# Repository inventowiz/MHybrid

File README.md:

MHybrid
=======

Repository for code/work done for the Michigan Hybrid Racing Team
=======

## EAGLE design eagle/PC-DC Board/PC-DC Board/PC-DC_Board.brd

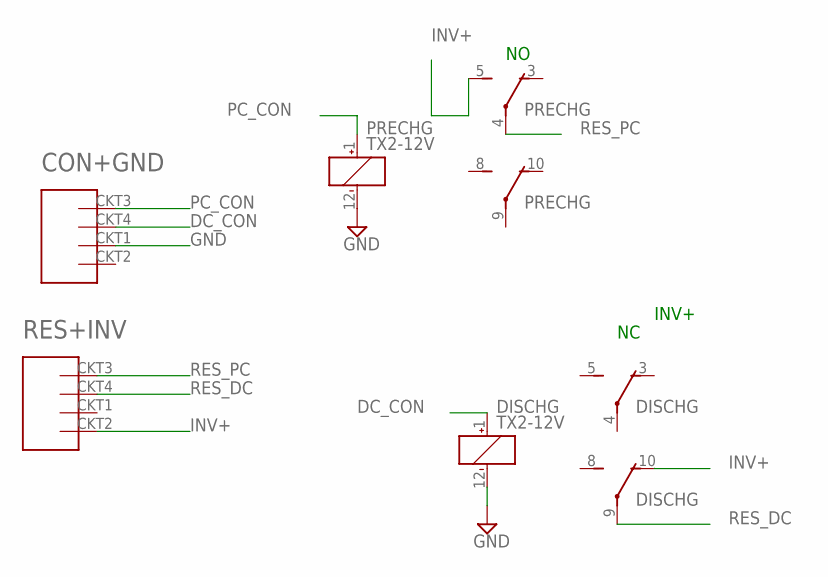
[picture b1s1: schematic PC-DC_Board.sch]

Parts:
CON+GND: MHYBRIDMOLEX; MOLEXMINIFIT6
DISCHG: TX2-12V; TX2
PRECHG: TX2-12V; TX2
RES+INV: MHYBRIDMOLEX; MOLEXMINIFIT6

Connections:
DC_CON: CON+GND.CKT4 (V_IN2(12)), DISCHG.1 (+)
GND: CON+GND.CKT1 (GND), DISCHG.12 (-), PRECHG.12 (-)
INV+: DISCHG.10 (O), PRECHG.5 (S), RES+INV.CKT2 (GND2)
PC_CON: CON+GND.CKT3 (V_IN(12)), PRECHG.1 (+)
RES_DC: DISCHG.9, RES+INV.CKT4 (V_IN2(12))
RES_PC: PRECHG.4, RES+INV.CKT3 (V_IN(12))

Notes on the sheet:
INV+

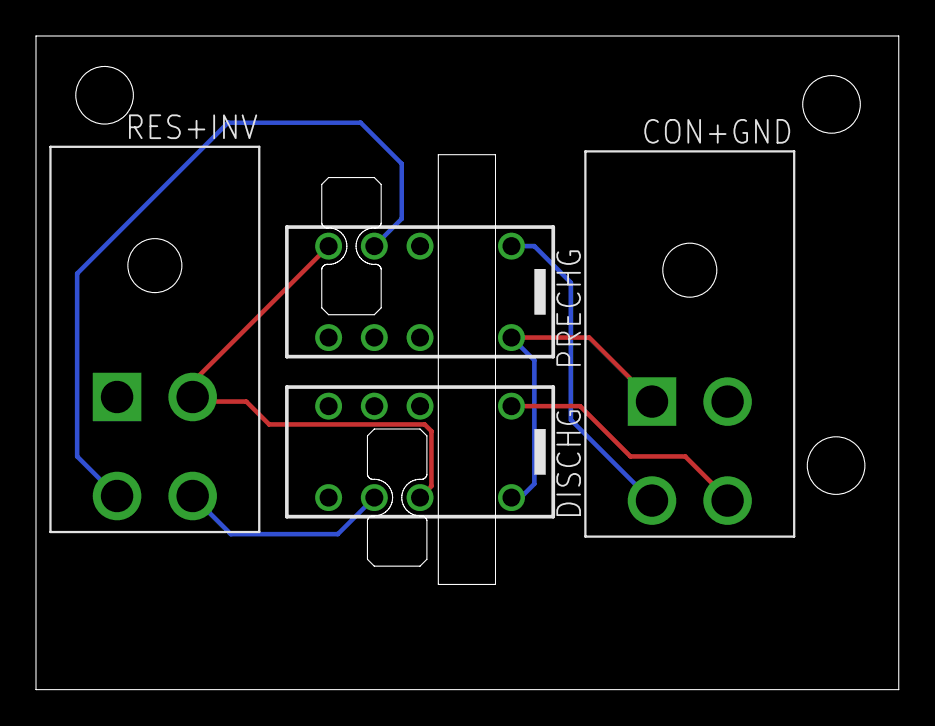
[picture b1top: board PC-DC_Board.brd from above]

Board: 2 copper layers, 47.9 x 36.3 mm, 4 parts (0 on the bottom side), 6 nets.

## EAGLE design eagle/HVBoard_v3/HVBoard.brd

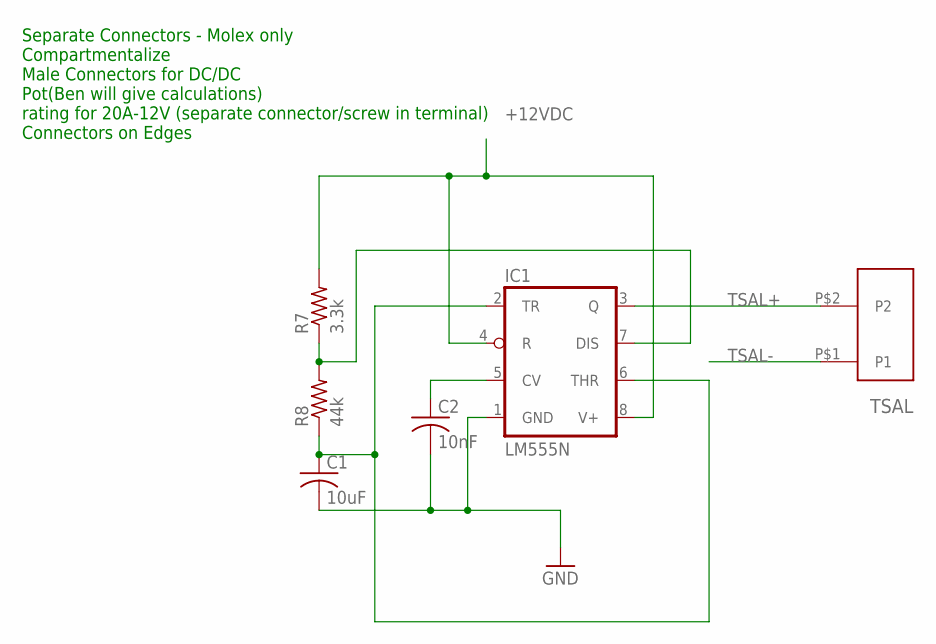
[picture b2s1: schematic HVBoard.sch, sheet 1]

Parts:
C1: 10uF; C025-025X050
C2: 10nF; C025-025X050
IC1: LM555N; DIL08
R7: 3.3k; 0207/7
R8: 44k; 0207/7
TSAL: MINIFIT_2PIN; 2PIN_MOLEXMINIFIT

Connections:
+12VDC: IC1.4 (R), IC1.8 (V+), R7.2; also elsewhere on the board
GND: C1.2, C2.2, IC1.1 (GND); also elsewhere on the board
unnamed: C1.1, IC1.2 (TR), IC1.6 (THR), R8.1
unnamed: IC1.7 (DIS), R7.1, R8.2
unnamed: C2.1, IC1.5 (CV)
TSAL+: IC1.3 (Q), TSAL.P$2 (P2)
TSAL-: TSAL.P$1 (P1); also elsewhere on the board

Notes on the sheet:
Separate Connectors - Molex only Compartmentalize Male Connectors for DC/DC Pot(Ben will give calculations) rating for 20A-12V (separate connector/screw in terminal) Connectors on Edges

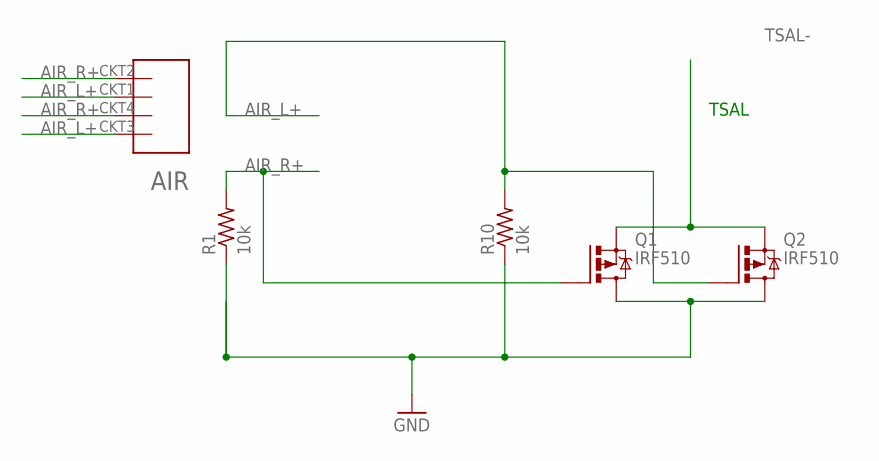
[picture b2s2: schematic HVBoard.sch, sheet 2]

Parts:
AIR: MHYBRIDMOLEX; MOLEXMINIFIT6
Q1, Q2: IRF510; TO220BV
R1, R10: 10k; 0207/7

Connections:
AIR_L+: AIR.CKT1 (GND), AIR.CKT3 (V_IN(12)), Q2.G, R10.2
AIR_R+: AIR.CKT2 (GND2), AIR.CKT4 (V_IN2(12)), Q1.G, R1.2
GND: Q1.D, Q2.D, R1.1, R10.1; also elsewhere on the board
TSAL-: Q1.S, Q2.S; also elsewhere on the board

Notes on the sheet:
TSAL

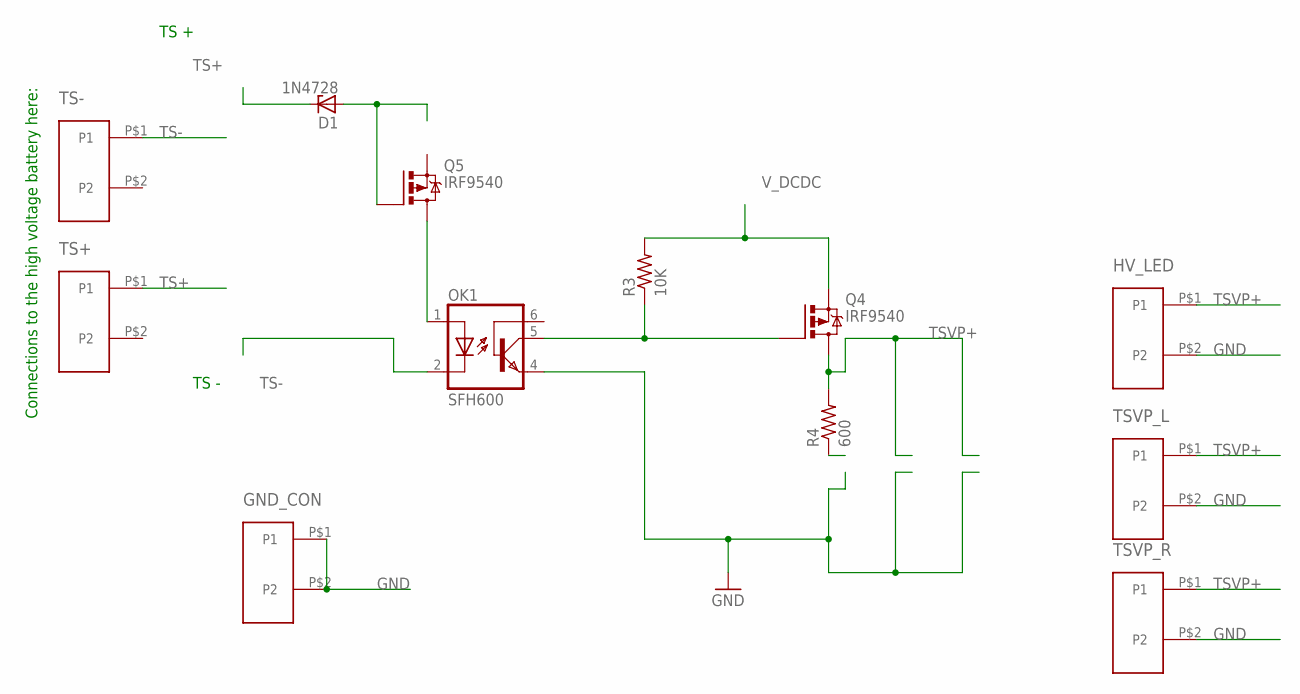
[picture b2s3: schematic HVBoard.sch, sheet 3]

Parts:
D1: 1N4728; DO41Z10
GND_CON: MINIFIT_2PIN; 2PIN_MOLEXMINIFIT
HV_LED: MINIFIT_2PIN; 2PIN_MOLEXMINIFIT
OK1: SFH600; DIL06
Q4, Q5: IRF9540; TO220BV
R3: 10K; R0603
R4: 600; R0603
TS+: MINIFIT_2PIN; 2PIN_MOLEXMINIFIT
TS-: MINIFIT_2PIN; 2PIN_MOLEXMINIFIT
TSVP_L: MINIFIT_2PIN; 2PIN_MOLEXMINIFIT
TSVP_R: MINIFIT_2PIN; 2PIN_MOLEXMINIFIT

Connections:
GND: GND_CON.P$1 (P1), GND_CON.P$2 (P2), HV_LED.P$2 (P2), OK1.4 (EMI), TSVP_L.P$2 (P2), TSVP_R.P$2 (P2); also elsewhere on the board
unnamed: OK1.5 (COL), Q4.G, R3.1
TS+: D1.C, TS+.P$1 (P1); also elsewhere on the board
TS+2: D1.A, Q5.G
TS+3: OK1.1 (A), Q5.D
TS-: OK1.2 (C), TS-.P$1 (P1); also elsewhere on the board
TSVP+: HV_LED.P$1 (P1), Q4.D, R4.2, TSVP_L.P$1 (P1), TSVP_R.P$1 (P1)
V_DCDC: Q4.S, R3.2; also elsewhere on the board

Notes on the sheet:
TS +
TS -
Connections to the high voltage battery here:

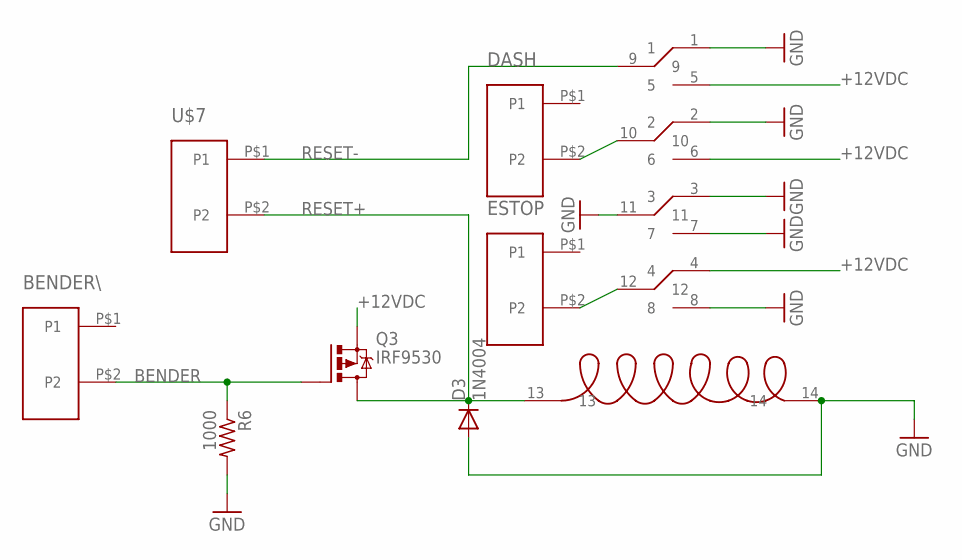
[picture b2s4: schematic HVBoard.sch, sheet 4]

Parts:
BENDER\: MINIFIT_2PIN; 2PIN_MOLEXMINIFIT
D3: 1N4004; DO41-10
DASH: MINIFIT_2PIN; 2PIN_MOLEXMINIFIT
ESTOP: MINIFIT_2PIN; 2PIN_MOLEXMINIFIT
NEW??1: HJ4-DC12VHJ4-DC12V; HJ4-DC12V
Q3: IRF9530; TO220BV
R6: 1000; M5923
U$7: MINIFIT_2PIN; 2PIN_MOLEXMINIFIT

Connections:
+12VDC: NEW??1.4, NEW??1.5, NEW??1.6, Q3.S; also elsewhere on the board
BENDER: BENDER\.P$2 (P2), Q3.G, R6.1
GND: D3.A, NEW??1.1, NEW??1.2, NEW??1.3, NEW??1.7, NEW??1.8, NEW??1.11, NEW??1.14, R6.2; also elsewhere on the board
unnamed: DASH.P$2 (P2), NEW??1.10
unnamed: ESTOP.P$2 (P2), NEW??1.12
RESET+: D3.C, NEW??1.13, Q3.D, U$7.P$2 (P2)
RESET-: NEW??1.9, U$7.P$1 (P1)

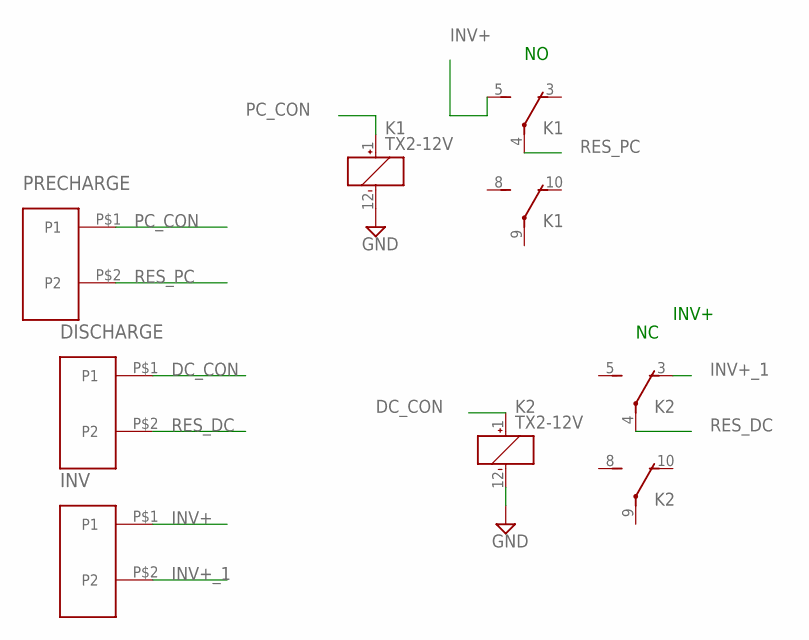
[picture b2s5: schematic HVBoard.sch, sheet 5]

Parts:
DISCHARGE: MINIFIT_2PIN; 2PIN_MOLEXMINIFIT
INV: MINIFIT_2PIN; 2PIN_MOLEXMINIFIT
K1, K2: TX2-12V; TX2
PRECHARGE: MINIFIT_2PIN; 2PIN_MOLEXMINIFIT

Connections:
DC_CON: DISCHARGE.P$1 (P1), K2.1 (+)
GND: K1.12 (-), K2.12 (-); also elsewhere on the board
INV+: INV.P$1 (P1), K1.5 (S)
INV+_1: INV.P$2 (P2), K2.3 (O)
PC_CON: K1.1 (+), PRECHARGE.P$1 (P1)
RES_DC: DISCHARGE.P$2 (P2), K2.4
RES_PC: K1.4, PRECHARGE.P$2 (P2)

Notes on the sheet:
INV+

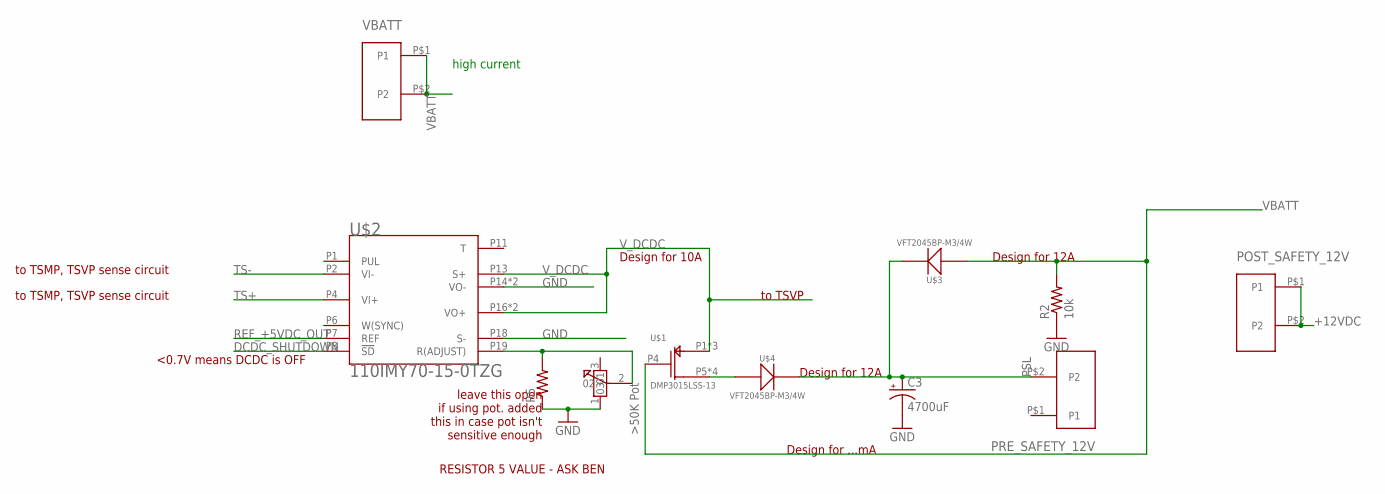
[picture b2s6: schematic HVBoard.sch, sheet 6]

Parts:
C3: 4700uF; CPOL-RADIAL-1000UF-63V
POST_SAFETY_12V: MINIFIT_2PIN; 2PIN_MOLEXMINIFIT
POT1: 3310P-001-503L-NP
PRE_SAFETY_12V: MINIFIT_2PIN; 2PIN_MOLEXMINIFIT
R2: 10k; R0603
R5: R-US_R0805; R0805
U$1: DMP3015LSS-13; 8-SOP
U$2: 110IMY70-15-0TZG
U$3, U$4: VFT2045BP-M3/4W
VBATT: MINIFIT_2PIN; 2PIN_MOLEXMINIFIT

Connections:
+12VDC: POST_SAFETY_12V.P$1 (P1), POST_SAFETY_12V.P$2 (P2); also elsewhere on the board
DCDC_SHUTDOWN: U$2.P8 (!SD)
GND: C3.2 (-), POT1.1, R2.1, R5.1, U$2.P14 (VO-), U$2.P15 (VO-), U$2.P18 (S-); also elsewhere on the board
unnamed: POT1.2, R5.2, U$2.P19 (R(ADJUST))
unnamed: U$1.P5 (D), U$1.P6 (D), U$1.P7 (D), U$1.P8 (D), U$4.P1
PSL: C3.1 (+), PRE_SAFETY_12V.P$2 (P2), U$3.P2, U$4.P2
REF_+5VDC_OUT: U$2.P7 (REF)
TS+: U$2.P4 (VI+); also elsewhere on the board
TS-: U$2.P2 (VI-); also elsewhere on the board
VBATT: R2.2, U$1.P4 (G), U$3.P1, VBATT.P$1 (P1), VBATT.P$2 (P2)
V_DCDC: U$1.P1 (S), U$1.P2 (S), U$1.P3 (S), U$2.P13 (S+), U$2.P16 (VO+), U$2.P17 (VO+); also elsewhere on the board

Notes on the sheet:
Design for 10A
Design for 12A
Design for ...mA
leave this open if using pot. added this in case pot isn't sensitive enough
<0.7V means DCDC is OFF
to TSVP
to TSMP, TSVP sense circuit
high current
RESISTOR 5 VALUE - ASK BEN

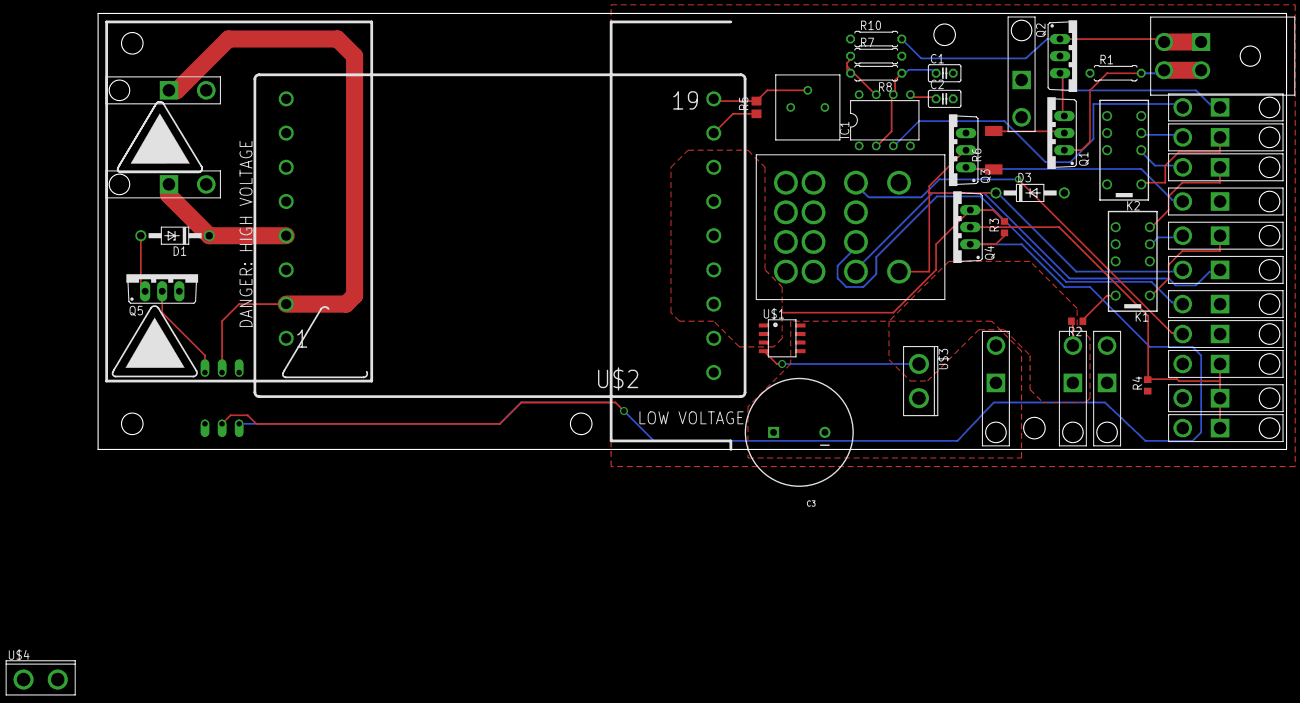
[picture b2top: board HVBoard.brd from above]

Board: 2 copper layers, 176.5 x 64.8 mm, 47 parts (1 on the bottom side), 31 nets.

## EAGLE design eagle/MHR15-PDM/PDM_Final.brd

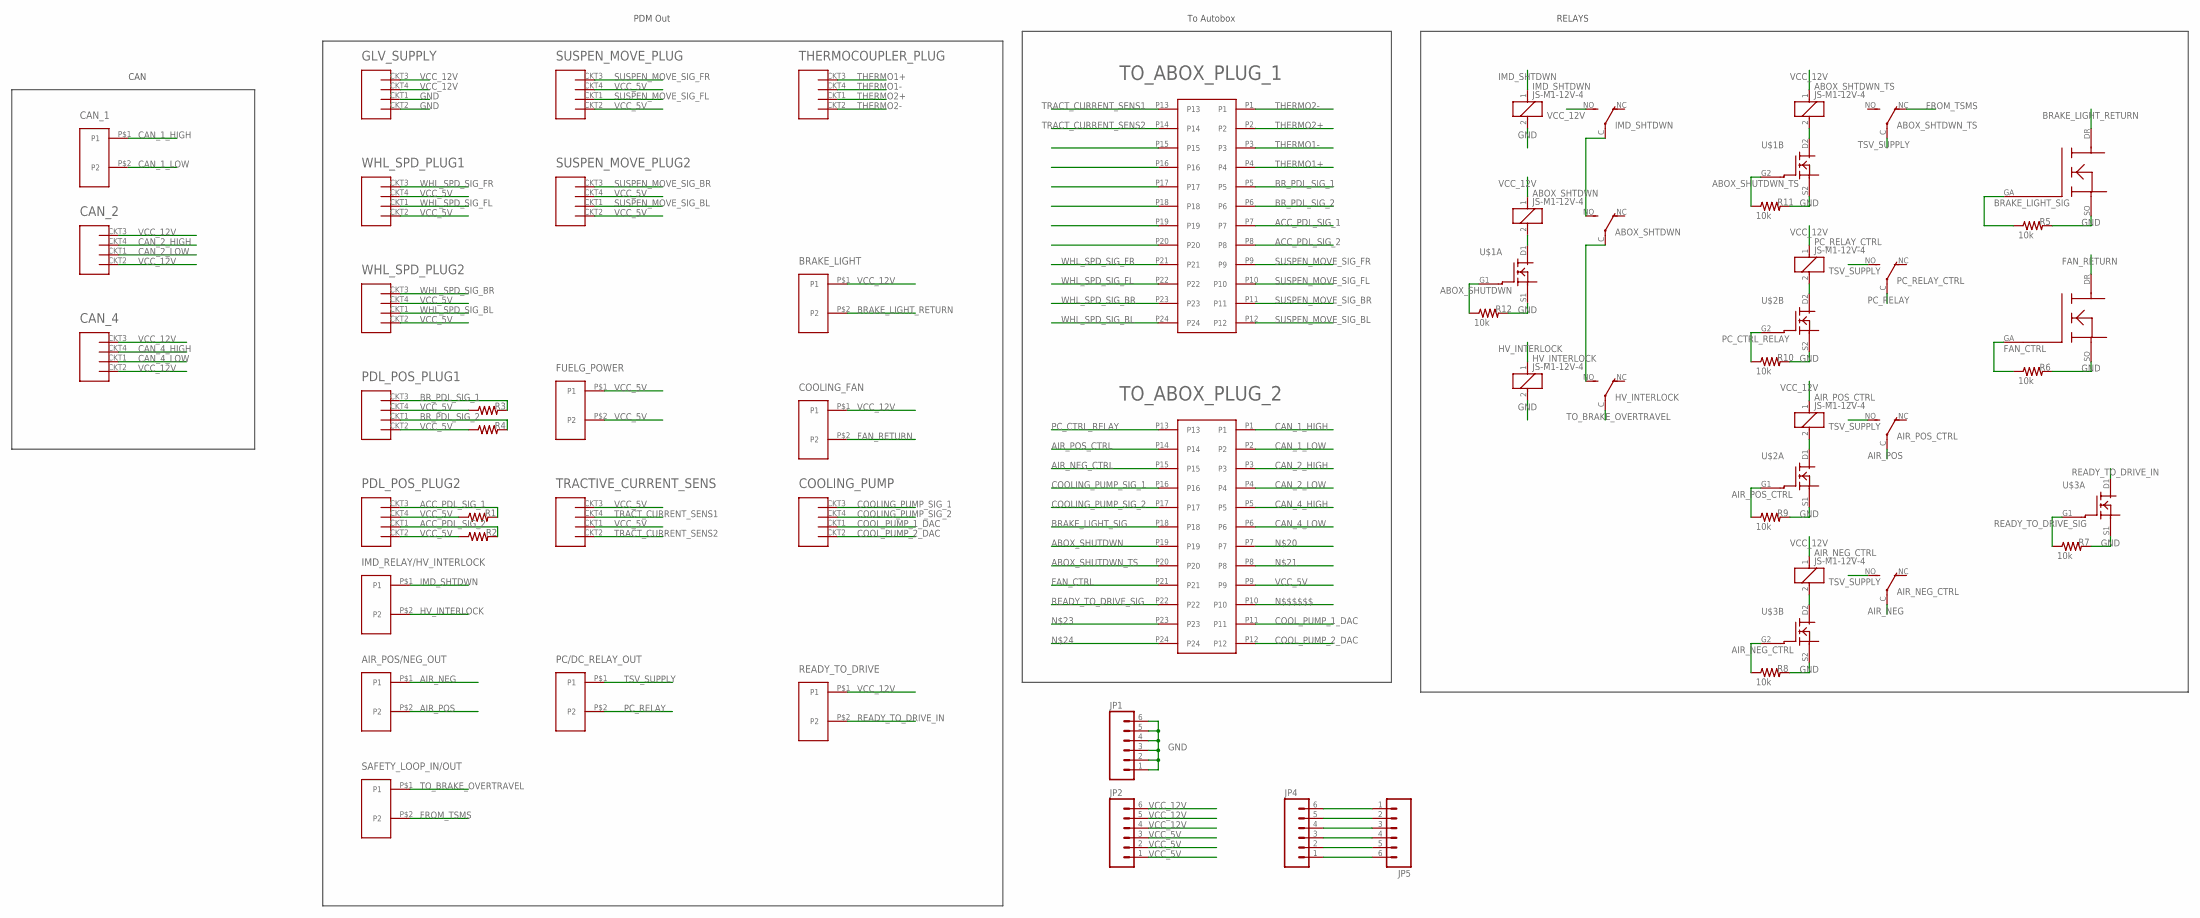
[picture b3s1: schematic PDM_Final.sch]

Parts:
ABOX_SHTDWN: JS-M1-12V-4; JS-M
ABOX_SHTDWN_TS: JS-M1-12V-4; JS-M
AIR_NEG_CTRL: JS-M1-12V-4; JS-M
AIR_POS/NEG_OUT: MINIFIT_2PIN; 2PIN_MOLEXMINIFIT
AIR_POS_CTRL: JS-M1-12V-4; JS-M
BRAKE_LIGHT: MINIFIT_2PIN; 2PIN_MOLEXMINIFIT
CAN_1: MINIFIT_2PIN; 2PIN_MOLEXMINIFIT
CAN_2, CAN_4: MHYBRIDMOLEX; MOLEXMINIFIT6
COOLING_FAN: MINIFIT_2PIN; 2PIN_MOLEXMINIFIT
COOLING_PUMP: MHYBRIDMOLEX; MOLEXMINIFIT6
FUELG_POWER: MINIFIT_2PIN; 2PIN_MOLEXMINIFIT
GLV_SUPPLY: MHYBRIDMOLEX; MOLEXMINIFIT6
HV_INTERLOCK: JS-M1-12V-4; JS-M
IMD_RELAY/HV_INTERLOCK: MINIFIT_2PIN; 2PIN_MOLEXMINIFIT
IMD_SHTDWN: JS-M1-12V-4; JS-M
JP1, JP2, JP4, JP5: M06LOCK; 1X06_LOCK
PC/DC_RELAY_OUT: MINIFIT_2PIN; 2PIN_MOLEXMINIFIT
PC_RELAY_CTRL: JS-M1-12V-4; JS-M
PDL_POS_PLUG1, PDL_POS_PLUG2: MHYBRIDMOLEX; MOLEXMINIFIT6
R1, R2, R3, R4: R-US_0204/2V; 0204V
R5, R6, R7, R8, R9, R10, R11, R12: 10k; 0204V
READY_TO_DRIVE: MINIFIT_2PIN; 2PIN_MOLEXMINIFIT
SAFETY_LOOP_IN/OUT: MINIFIT_2PIN; 2PIN_MOLEXMINIFIT
SUSPEN_MOVE_PLUG, SUSPEN_MOVE_PLUG2: MHYBRIDMOLEX; MOLEXMINIFIT6
THERMOCOUPLER_PLUG: MHYBRIDMOLEX; MOLEXMINIFIT6
TO_ABOX_PLUG_1, TO_ABOX_PLUG_2: 24PIN_MOLEX
TRACTIVE_CURRENT_SENS: MHYBRIDMOLEX; MOLEXMINIFIT6
U$1, U$2, U$3: COMBINED_TRANSIS; TRANSIS_6
U$4, U$5: HIGH_AMP_TRANS
WHL_SPD_PLUG1, WHL_SPD_PLUG2: MHYBRIDMOLEX; MOLEXMINIFIT6

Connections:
ABOX_SHUTDWN: R12.1, TO_ABOX_PLUG_2.P19, U$1.G1 (GA)
ABOX_SHUTDWN_TS: R11.1, TO_ABOX_PLUG_2.P20, U$1.G2 (GA)
ACC_PDL_SIG_1: PDL_POS_PLUG2.CKT3 (V_IN(12)), R1.2, TO_ABOX_PLUG_1.P7
ACC_PDL_SIG_2: PDL_POS_PLUG2.CKT1 (GND), R2.2, TO_ABOX_PLUG_1.P8
AIR_NEG: AIR_NEG_CTRL.C, AIR_POS/NEG_OUT.P$1 (P1)
AIR_NEG_CTRL: R8.1, TO_ABOX_PLUG_2.P15, U$3.G2 (GA)
AIR_POS: AIR_POS/NEG_OUT.P$2 (P2), AIR_POS_CTRL.C
AIR_POS_CTRL: R9.1, TO_ABOX_PLUG_2.P14, U$2.G1 (GA)
BRAKE_LIGHT_RETURN: BRAKE_LIGHT.P$2 (P2), U$4.DR
BRAKE_LIGHT_SIG: R5.1, TO_ABOX_PLUG_2.P18, U$4.GA
BR_PDL_SIG_1: PDL_POS_PLUG1.CKT3 (V_IN(12)), R3.2, TO_ABOX_PLUG_1.P5
BR_PDL_SIG_2: PDL_POS_PLUG1.CKT1 (GND), R4.2, TO_ABOX_PLUG_1.P6
CAN_1_HIGH: CAN_1.P$1 (P1), TO_ABOX_PLUG_2.P1
CAN_1_LOW: CAN_1.P$2 (P2), TO_ABOX_PLUG_2.P2
CAN_2_HIGH: CAN_2.CKT4 (V_IN2(12)), TO_ABOX_PLUG_2.P3
CAN_2_LOW: CAN_2.CKT1 (GND), TO_ABOX_PLUG_2.P4
CAN_4_HIGH: CAN_4.CKT4 (V_IN2(12)), TO_ABOX_PLUG_2.P5
CAN_4_LOW: CAN_4.CKT1 (GND), TO_ABOX_PLUG_2.P6
COOLING_PUMP_SIG_1: COOLING_PUMP.CKT3 (V_IN(12)), TO_ABOX_PLUG_2.P16
COOLING_PUMP_SIG_2: COOLING_PUMP.CKT4 (V_IN2(12)), TO_ABOX_PLUG_2.P17
COOL_PUMP_1_DAC: COOLING_PUMP.CKT1 (GND), TO_ABOX_PLUG_2.P11
COOL_PUMP_2_DAC: COOLING_PUMP.CKT2 (GND2), TO_ABOX_PLUG_2.P12
FAN_CTRL: R6.1, TO_ABOX_PLUG_2.P21, U$5.GA
FAN_RETURN: COOLING_FAN.P$2 (P2), U$5.DR
FROM_TSMS: ABOX_SHTDWN_TS.NC (O), SAFETY_LOOP_IN/OUT.P$2 (P2)
GND: GLV_SUPPLY.CKT1 (GND), GLV_SUPPLY.CKT2 (GND2), HV_INTERLOCK.2, IMD_SHTDWN.2, JP1.1, JP1.2, JP1.3, JP1.4, JP1.5, JP1.6, R5.2, R6.2, R7.2, R8.2, R9.2, R10.2, R11.2, R12.2, U$1.S1 (SO), U$1.S2 (SO), U$2.S1 (SO), U$2.S2 (SO), U$3.S1 (SO), U$3.S2 (SO), U$4.SO, U$5.SO
HV_INTERLOCK: HV_INTERLOCK.1, IMD_RELAY/HV_INTERLOCK.P$2 (P2)
IMD_SHTDWN: IMD_RELAY/HV_INTERLOCK.P$1 (P1), IMD_SHTDWN.1
unnamed: ABOX_SHTDWN.2, U$1.D1 (DR)
unnamed: ABOX_SHTDWN.NO (S), IMD_SHTDWN.C
unnamed: ABOX_SHTDWN.C, HV_INTERLOCK.NO (S)
unnamed: ABOX_SHTDWN_TS.2, U$1.D2 (DR)
unnamed: PC_RELAY_CTRL.2, U$2.D2 (DR)
unnamed: AIR_POS_CTRL.2, U$2.D1 (DR)
unnamed: AIR_NEG_CTRL.2, U$3.D2 (DR)
unnamed: JP4.6, JP5.1
unnamed: JP4.5, JP5.2
unnamed: JP4.4, JP5.3
unnamed: JP4.3, JP5.4
unnamed: JP4.2, JP5.5
unnamed: JP4.1, JP5.6
N$$$$$$: TO_ABOX_PLUG_2.P10
PC_CTRL_RELAY: R10.1, TO_ABOX_PLUG_2.P13, U$2.G2 (GA)
PC_RELAY: PC/DC_RELAY_OUT.P$2 (P2), PC_RELAY_CTRL.C
READY_TO_DRIVE_IN: READY_TO_DRIVE.P$2 (P2), U$3.D1 (DR)
READY_TO_DRIVE_SIG: R7.1, TO_ABOX_PLUG_2.P22, U$3.G1 (GA)
SUSPEN_MOVE_SIG_BL: SUSPEN_MOVE_PLUG2.CKT1 (GND), TO_ABOX_PLUG_1.P12
SUSPEN_MOVE_SIG_BR: SUSPEN_MOVE_PLUG2.CKT3 (V_IN(12)), TO_ABOX_PLUG_1.P11
SUSPEN_MOVE_SIG_FL: SUSPEN_MOVE_PLUG.CKT1 (GND), TO_ABOX_PLUG_1.P10
SUSPEN_MOVE_SIG_FR: SUSPEN_MOVE_PLUG.CKT3 (V_IN(12)), TO_ABOX_PLUG_1.P9
THERMO1+: THERMOCOUPLER_PLUG.CKT3 (V_IN(12)), TO_ABOX_PLUG_1.P4
THERMO1-: THERMOCOUPLER_PLUG.CKT4 (V_IN2(12)), TO_ABOX_PLUG_1.P3
THERMO2+: THERMOCOUPLER_PLUG.CKT1 (GND), TO_ABOX_PLUG_1.P2
THERMO2-: THERMOCOUPLER_PLUG.CKT2 (GND2), TO_ABOX_PLUG_1.P1
TO_BRAKE_OVERTRAVEL: HV_INTERLOCK.C, SAFETY_LOOP_IN/OUT.P$1 (P1)
TRACT_CURRENT_SENS1: TO_ABOX_PLUG_1.P13, TRACTIVE_CURRENT_SENS.CKT4 (V_IN2(12))
TRACT_CURRENT_SENS2: TO_ABOX_PLUG_1.P14, TRACTIVE_CURRENT_SENS.CKT2 (GND2)
TSV_SUPPLY: ABOX_SHTDWN_TS.C, AIR_NEG_CTRL.NO (S), AIR_POS_CTRL.NO (S), PC/DC_RELAY_OUT.P$1 (P1), PC_RELAY_CTRL.NO (S)
VCC_5V: FUELG_POWER.P$1 (P1), FUELG_POWER.P$2 (P2), JP2.1, JP2.2, JP2.3, PDL_POS_PLUG1.CKT2 (GND2), PDL_POS_PLUG1.CKT4 (V_IN2(12)), PDL_POS_PLUG2.CKT2 (GND2), PDL_POS_PLUG2.CKT4 (V_IN2(12)), R1.1, R2.1, R3.1, R4.1, SUSPEN_MOVE_PLUG.CKT2 (GND2), SUSPEN_MOVE_PLUG.CKT4 (V_IN2(12)), SUSPEN_MOVE_PLUG2.CKT2 (GND2), SUSPEN_MOVE_PLUG2.CKT4 (V_IN2(12)), TO_ABOX_PLUG_2.P9, TRACTIVE_CURRENT_SENS.CKT1 (GND), TRACTIVE_CURRENT_SENS.CKT3 (V_IN(12)), WHL_SPD_PLUG1.CKT2 (GND2), WHL_SPD_PLUG1.CKT4 (V_IN2(12)), WHL_SPD_PLUG2.CKT2 (GND2), WHL_SPD_PLUG2.CKT4 (V_IN2(12))
VCC_12V: ABOX_SHTDWN.1, ABOX_SHTDWN_TS.1, AIR_NEG_CTRL.1, AIR_POS_CTRL.1, BRAKE_LIGHT.P$1 (P1), CAN_2.CKT2 (GND2), CAN_2.CKT3 (V_IN(12)), CAN_4.CKT2 (GND2), CAN_4.CKT3 (V_IN(12)), COOLING_FAN.P$1 (P1), GLV_SUPPLY.CKT3 (V_IN(12)), GLV_SUPPLY.CKT4 (V_IN2(12)), IMD_SHTDWN.NO (S), JP2.4, JP2.5, JP2.6, PC_RELAY_CTRL.1, READY_TO_DRIVE.P$1 (P1)
WHL_SPD_SIG_BL: TO_ABOX_PLUG_1.P24, WHL_SPD_PLUG2.CKT1 (GND)
WHL_SPD_SIG_BR: TO_ABOX_PLUG_1.P23, WHL_SPD_PLUG2.CKT3 (V_IN(12))
WHL_SPD_SIG_FL: TO_ABOX_PLUG_1.P22, WHL_SPD_PLUG1.CKT1 (GND)
WHL_SPD_SIG_FR: TO_ABOX_PLUG_1.P21, WHL_SPD_PLUG1.CKT3 (V_IN(12))

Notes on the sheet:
PDM Out
To Autobox
RELAYS
CAN

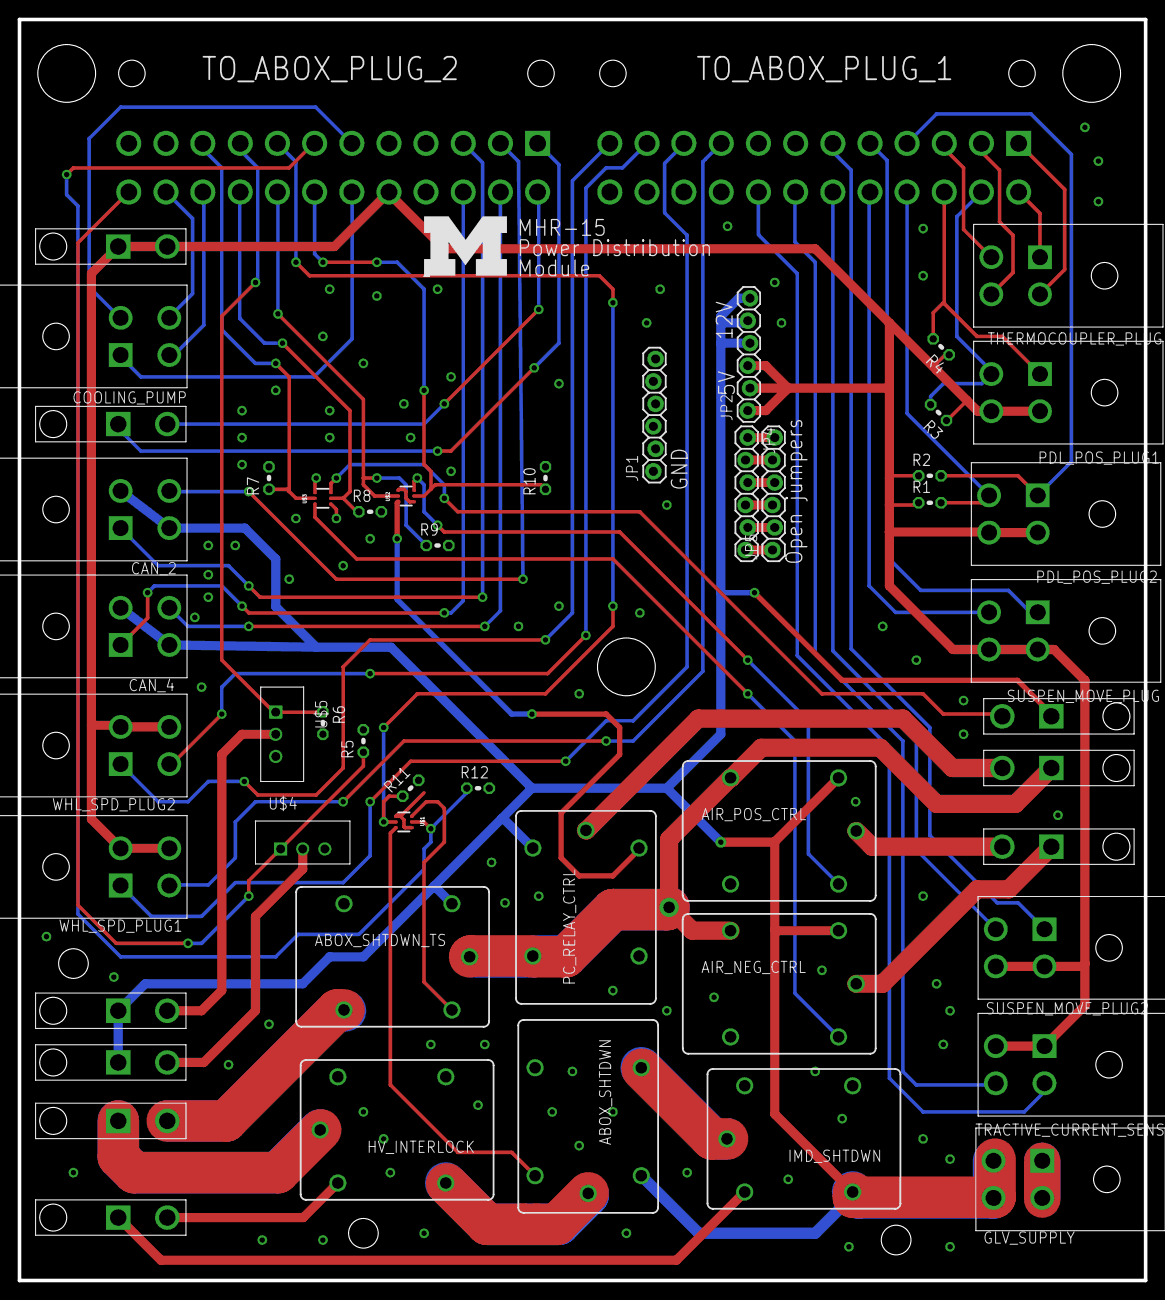
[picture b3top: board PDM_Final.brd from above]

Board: 2 copper layers, 127.3 x 142.5 mm, 52 parts (0 on the bottom side), 63 nets.

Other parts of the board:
U$6: BLOCKM

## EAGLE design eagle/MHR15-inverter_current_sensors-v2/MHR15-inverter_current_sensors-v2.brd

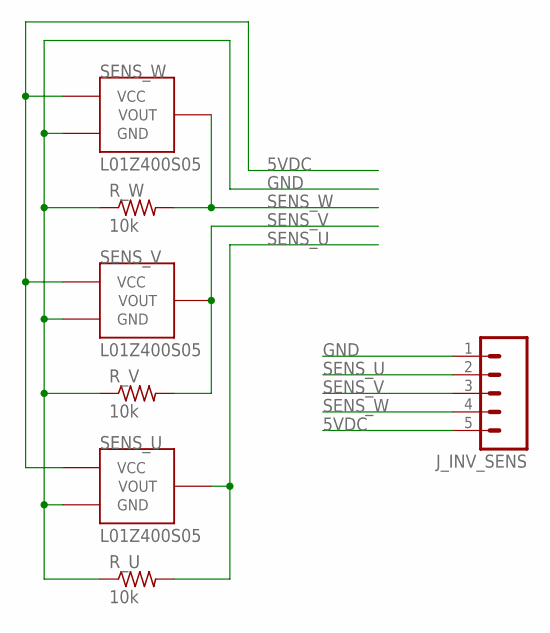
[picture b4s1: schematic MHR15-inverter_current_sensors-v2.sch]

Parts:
J_INV_SENS: M05LOCK; 1X05_LOCK
R_U: 10k; R0603
R_V: 10k; R0603
R_W: 10k; R0603
SENS_U: L01Z400S05
SENS_V: L01Z400S05
SENS_W: L01Z400S05

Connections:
5VDC: J_INV_SENS.5, SENS_U.VCC, SENS_V.VCC, SENS_W.VCC
GND: J_INV_SENS.1, R_U.1, R_V.1, R_W.1, SENS_U.GND, SENS_V.GND, SENS_W.GND
SENS_U: J_INV_SENS.2, R_U.2, SENS_U.VOUT
SENS_V: J_INV_SENS.3, R_V.2, SENS_V.VOUT
SENS_W: J_INV_SENS.4, R_W.2, SENS_W.VOUT

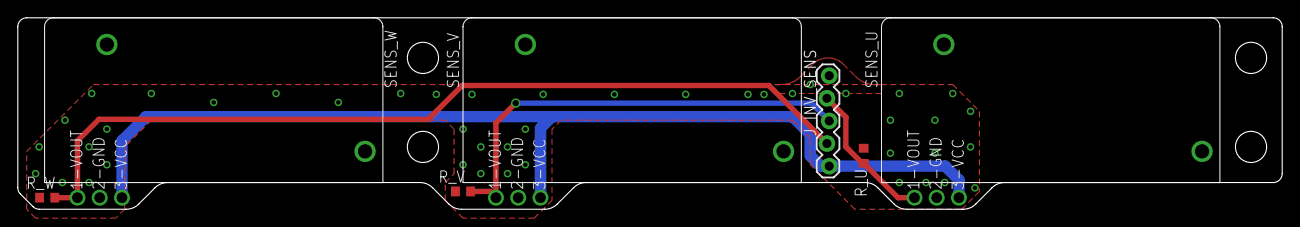
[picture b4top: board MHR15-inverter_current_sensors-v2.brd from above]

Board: 2 copper layers, 142.0 x 21.5 mm, 7 parts (0 on the bottom side), 5 nets.

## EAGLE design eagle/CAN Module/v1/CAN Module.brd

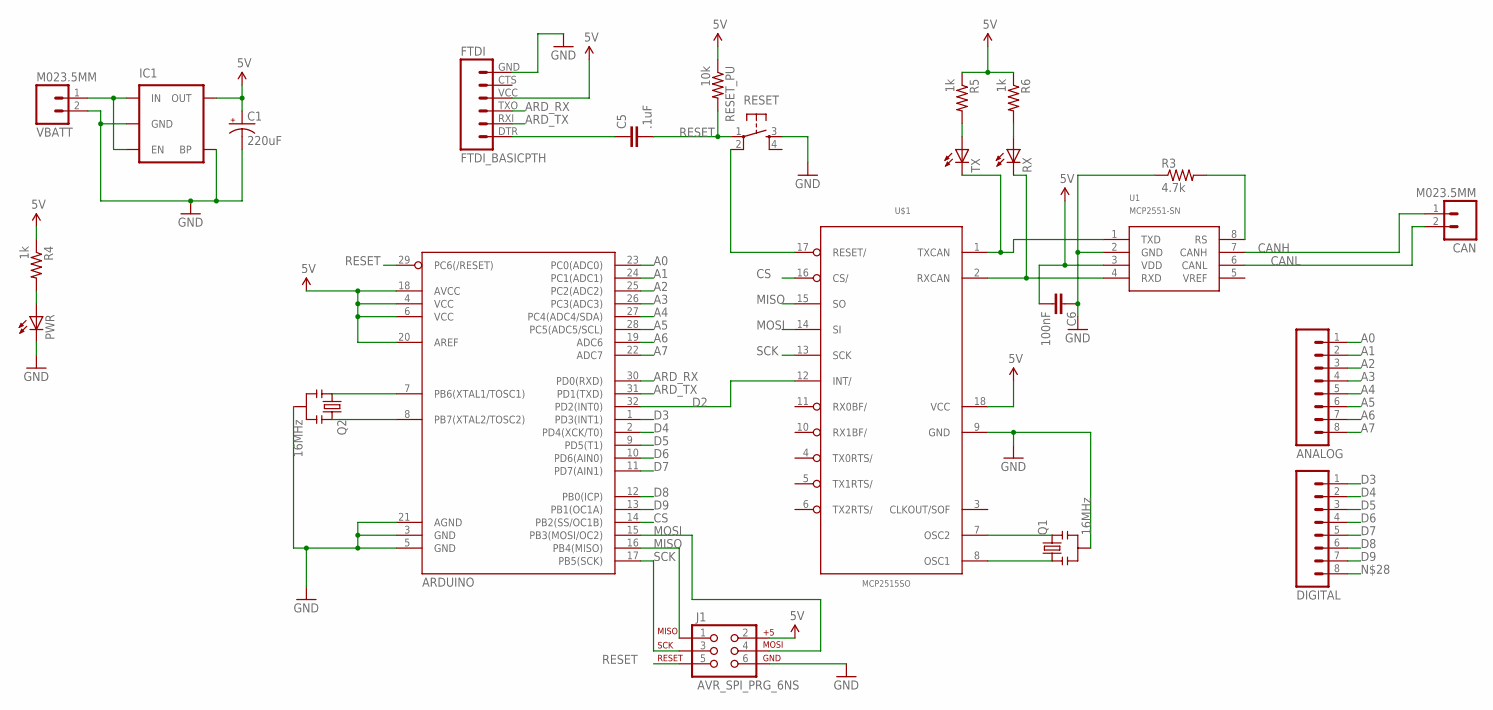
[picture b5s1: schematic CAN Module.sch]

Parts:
ANALOG: M08LOCK; 1X08_LOCK
ARDUINO: ATMEGA328_SMT; TQFP32-08
C1: 220uF; EIA3216-KIT
C5: .1uF; 0805
C6: 100nF; 0805
CAN: M023.5MM; SCREWTERMINAL-3.5MM-2
DIGITAL: M08LOCK; 1X08_LOCK
FTDI: FTDI_BASICPTH; FTDI_BASIC
IC1: MIC52055V; SOT23-5
J1: AVR_SPI_PRG_6NS; 2X3-NS
PWR: LEDCHIPLED_0805; CHIPLED_0805
Q1, Q2: 16MHz; RESONATOR-SMD
R3: 4.7k; 0805
R4, R5, R6: 1k; 0805
RESET: TAC_SWITCHSMD; TACTILE_SWITCH_SMD
RESET_PU: 10k; 0805
RX: LEDCHIPLED_0805; CHIPLED_0805
TX: LEDCHIPLED_0805; CHIPLED_0805
U1: MCP2551-SN; SO-08
U$1: MCP2515SO; SO18L
VBATT: M023.5MM; SCREWTERMINAL-3.5MM-2

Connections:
5V: ARDUINO.4 (VCC), ARDUINO.6 (VCC), ARDUINO.18 (AVCC), ARDUINO.20 (AREF), C1.A (+), C6.2, FTDI.VCC (4), IC1.5 (OUT), J1.2, R4.1, R5.1, R6.1, RESET_PU.1, U1.3 (VDD), U$1.18 (VCC)
A0: ANALOG.1, ARDUINO.23 (PC0(ADC0))
A1: ANALOG.2, ARDUINO.24 (PC1(ADC1))
A2: ANALOG.3, ARDUINO.25 (PC2(ADC2))
A3: ANALOG.4, ARDUINO.26 (PC3(ADC3))
A4: ANALOG.5, ARDUINO.27 (PC4(ADC4/SDA))
A5: ANALOG.6, ARDUINO.28 (PC5(ADC5/SCL))
A6: ANALOG.7, ARDUINO.19 (ADC6)
A7: ANALOG.8, ARDUINO.22 (ADC7)
ARD_RX: ARDUINO.30 (PD0(RXD)), FTDI.TXO (3)
ARD_TX: ARDUINO.31 (PD1(TXD)), FTDI.RXI (2)
CANH: CAN.1, U1.7 (CANH)
CANL: CAN.2, U1.6 (CANL)
CS: ARDUINO.14 (PB2(SS/OC1B)), U$1.16 (CS/)
D2: ARDUINO.32 (PD2(INT0)), U$1.12 (INT/)
D3: ARDUINO.1 (PD3(INT1)), DIGITAL.1
D4: ARDUINO.2 (PD4(XCK/T0)), DIGITAL.2
D5: ARDUINO.9 (PD5(T1)), DIGITAL.3
D6: ARDUINO.10 (PD6(AIN0)), DIGITAL.4
D7: ARDUINO.11 (PD7(AIN1)), DIGITAL.5
D8: ARDUINO.12 (PB0(ICP)), DIGITAL.6
D9: ARDUINO.13 (PB1(OC1A)), DIGITAL.7
GND: ARDUINO.3 (GND), ARDUINO.5 (GND), ARDUINO.21 (AGND), C1.C (-), C6.1, FTDI.GND (6), IC1.2 (GND), IC1.4 (BP), J1.6, PWR.C, Q1.2, Q2.2, R3.1, RESET.3, U1.2 (GND), U$1.9 (GND), VBATT.2
MISO: ARDUINO.16 (PB4(MISO)), J1.1, U$1.15 (SO)
MOSI: ARDUINO.15 (PB3(MOSI/OC2)), J1.4, U$1.14 (SI)
unnamed: RX.C, U1.4 (RXD), U$1.2 (RXCAN)
unnamed: TX.C, U1.1 (TXD), U$1.1 (TXCAN)
unnamed: RESET.2, U$1.17 (RESET/)
unnamed: ARDUINO.7 (PB6(XTAL1/TOSC1)), Q2.1
unnamed: ARDUINO.8 (PB7(XTAL2/TOSC2)), Q2.3
unnamed: C5.1, FTDI.DTR (1)
unnamed: Q1.3, U$1.7 (OSC2)
unnamed: Q1.1, U$1.8 (OSC1)
unnamed: IC1.1 (IN), IC1.3 (EN), VBATT.1
unnamed: R3.2, U1.8 (RS)
unnamed: PWR.A, R4.2
unnamed: R5.2, TX.A
unnamed: R6.2, RX.A
RESET: ARDUINO.29 (PC6(/RESET)), C5.2, J1.5, RESET.1, RESET_PU.2
SCK: ARDUINO.17 (PB5(SCK)), J1.3, U$1.13 (SCK)

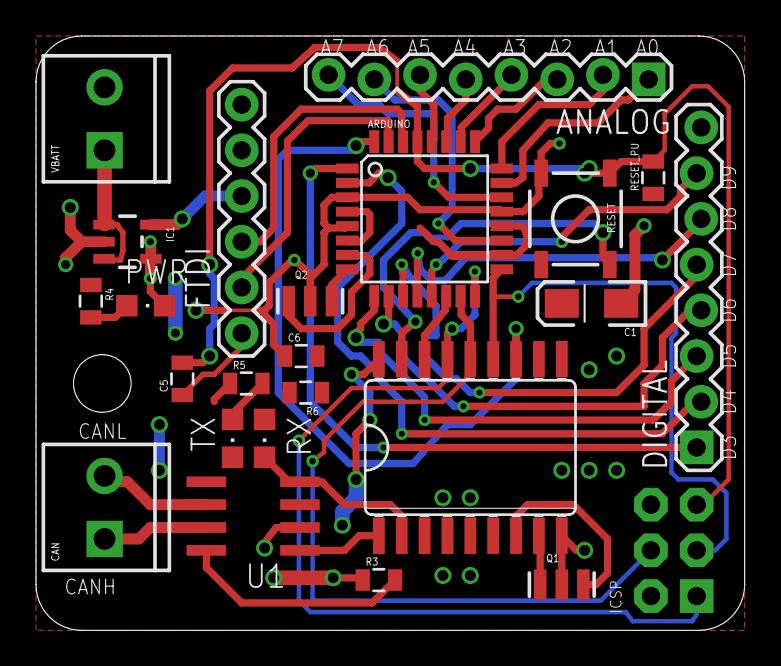
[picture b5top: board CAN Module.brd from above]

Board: 2 copper layers, 39.4 x 33.0 mm, 24 parts (0 on the bottom side), 40 nets.

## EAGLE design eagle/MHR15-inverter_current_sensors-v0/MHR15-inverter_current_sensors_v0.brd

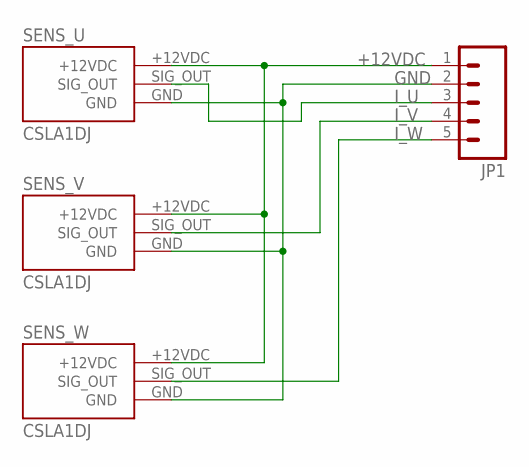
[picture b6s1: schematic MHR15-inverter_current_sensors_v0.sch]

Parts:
JP1: M05LOCK; 1X05_LOCK
SENS_U: CSLA1DJ
SENS_V: CSLA1DJ
SENS_W: CSLA1DJ

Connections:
+12VDC: JP1.1, SENS_U.+12VDC, SENS_V.+12VDC, SENS_W.+12VDC
GND: JP1.2, SENS_U.GND, SENS_V.GND, SENS_W.GND
I_U: JP1.3, SENS_U.SIG_OUT
I_V: JP1.4, SENS_V.SIG_OUT
I_W: JP1.5, SENS_W.SIG_OUT

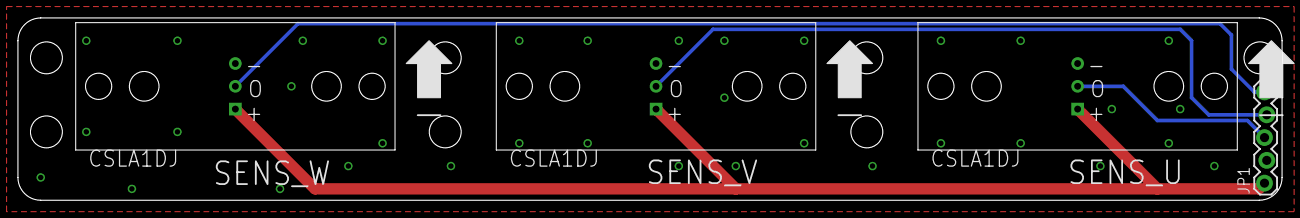
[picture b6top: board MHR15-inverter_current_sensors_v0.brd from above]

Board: 2 copper layers, 140.9 x 20.3 mm, 4 parts (0 on the bottom side), 5 nets.

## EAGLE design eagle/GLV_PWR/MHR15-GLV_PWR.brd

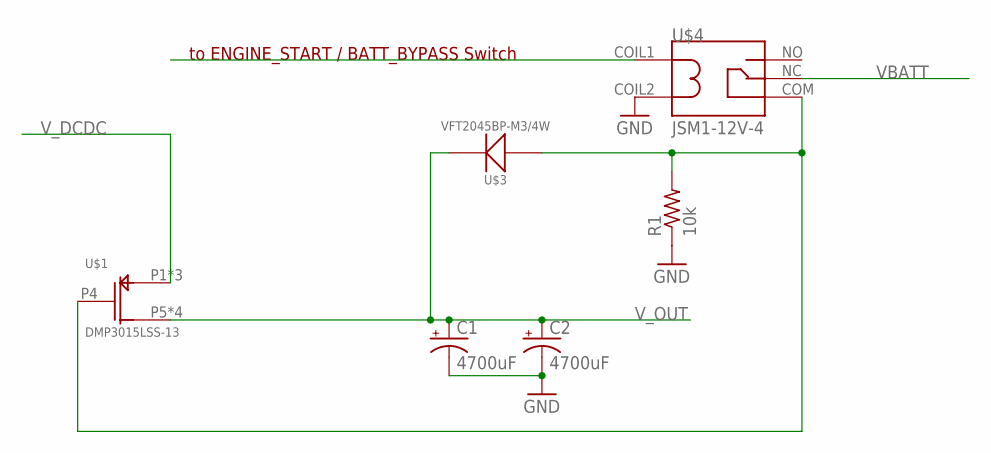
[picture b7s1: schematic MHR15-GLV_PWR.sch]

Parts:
C1, C2: 4700uF; CPOL-RADIAL-1000UF-63V
R1: 10k; R0603
U$1: DMP3015LSS-13; 8-SOP
U$3: VFT2045BP-M3/4W
U$4: JSM1-12V-4

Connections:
GND: C1.2 (-), C2.2 (-), R1.1, U$4.COIL2
unnamed: R1.2, U$1.P4 (G), U$3.P1, U$4.COM
VBATT: U$4.NC
V_DCDC: U$1.P1 (S), U$1.P2 (S), U$1.P3 (S)
V_OUT: C1.1 (+), C2.1 (+), U$1.P5 (D), U$1.P6 (D), U$1.P7 (D), U$1.P8 (D), U$3.P2

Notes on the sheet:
to ENGINE_START / BATT_BYPASS Switch

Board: 2 copper layers, 6 parts (0 on the bottom side), 4 nets, no tracks yet.

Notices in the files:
eagle/MHR15-inverter_current_sensors-v0/MHR15-inverter_current_sensors_v0.brd:
(c) 2014 Ben Wang
eagle/MHR15-inverter_current_sensors-v2/MHR15-inverter_current_sensors-v2.brd:
(c) 2015 Ben Wang
parts and their libraries:
SparkFun-DigitalIC: Licensing: CC v3.0 Share-Alike You are welcome to use this library for commercial purposes.
MHR15-GLV_PWR: (c)2014-2015 Ben Wang
SparkFun-Capacitors: Licensing: Creative Commons ShareAlike 4.0 International - https://creativecommons.org/licenses/by-sa/4.0
